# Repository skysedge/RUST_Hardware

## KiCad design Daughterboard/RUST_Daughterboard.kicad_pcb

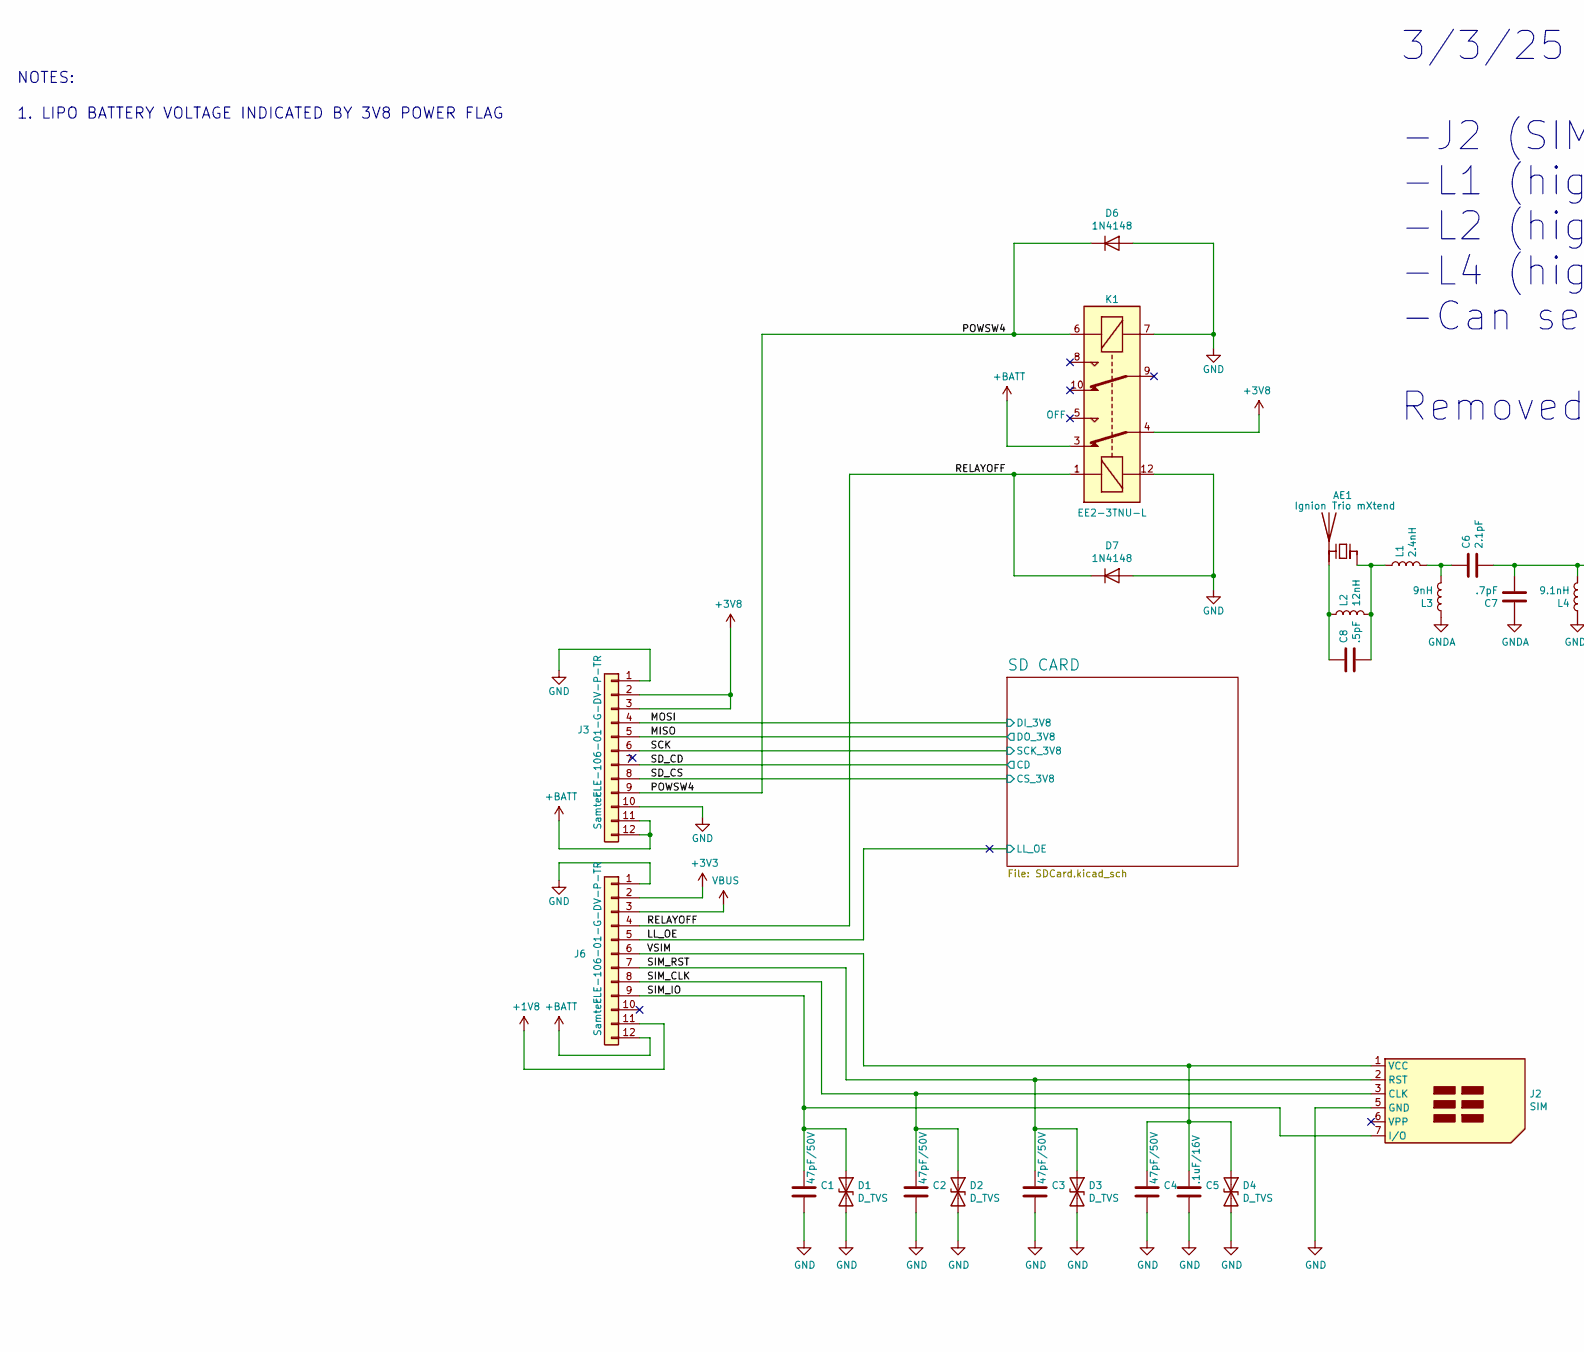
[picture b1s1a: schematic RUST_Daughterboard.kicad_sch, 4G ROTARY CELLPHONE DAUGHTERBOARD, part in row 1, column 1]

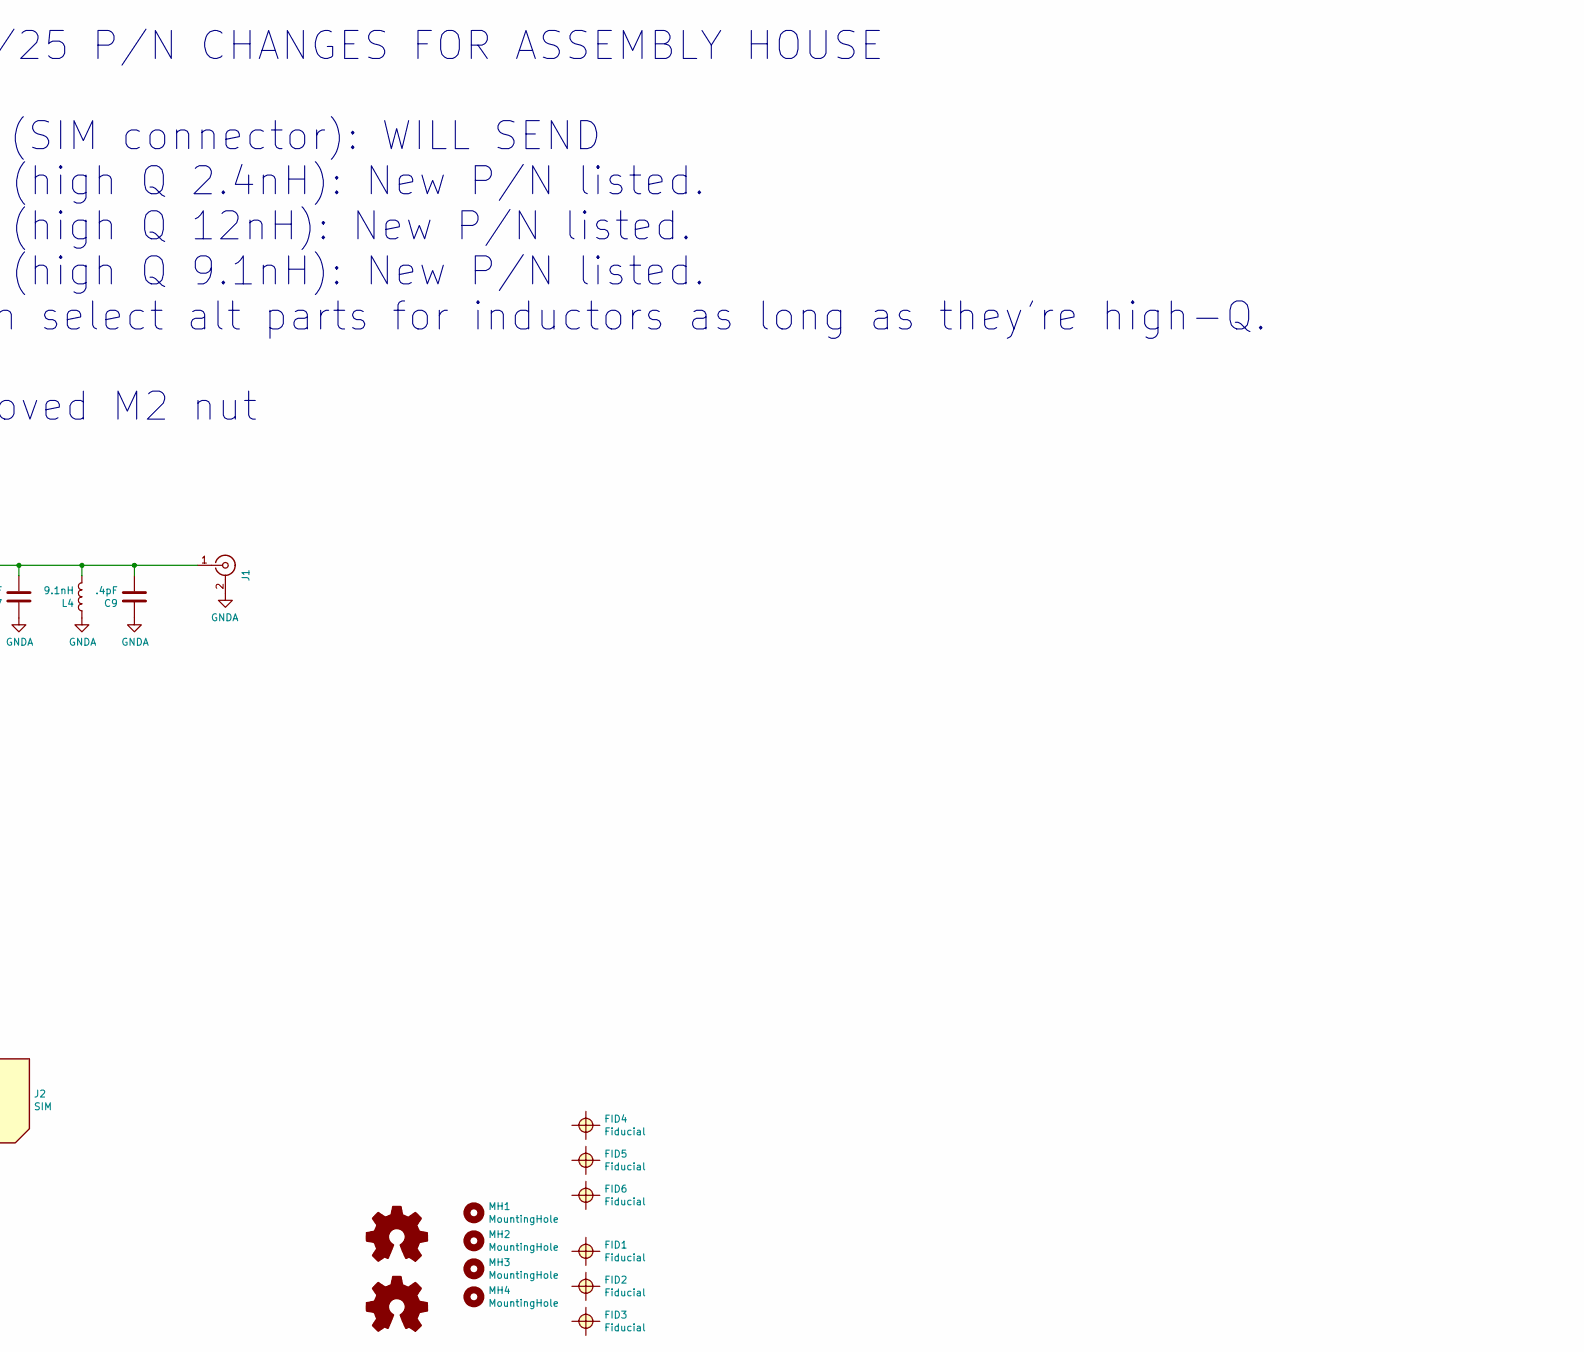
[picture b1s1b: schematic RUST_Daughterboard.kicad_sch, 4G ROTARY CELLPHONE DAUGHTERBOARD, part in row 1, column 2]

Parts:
AE1: Ignion Trio mXtend; Antenna_Ignion_TriomXtend_NN03-310; Mfg. Part No. NN03-310
C1, C2, C3, C4: 47pF/50V; C_0603_1608Metric; Mfg. Part No. GRM1555C1H470JA01D
C5: .1uF/16V; C_0603_1608Metric; Mfg. Part No. C0402C104K4RACTU
C6: 2.1pF; C_0402_1005Metric; Mfg. Part No. GJM1555C1H2R1BB01D
C7: .7pF; C_0402_1005Metric; Mfg. Part No. GJM1555C1HR70BB01D
C8: .5pF; C_0402_1005Metric; Mfg. Part No. 0402N8R2D500CT
C9: .4pF; C_0402_1005Metric; Mfg. Part No. GJM1555C1HR40WB01D
D1, D2, D3, D4: D_TVS; D_0603_1608Metric; Mfg. Part No. PESD0402-140
D6, D7: 1N4148; D_SOD-123; Mfg. Part No. 1N4148W-13-F
FID1, FID2, FID3, FID4, FID5, FID6: Fiducial; Fiducial_0.75mm_Dia_1.5mm_Outer
J1: Conn_Coaxial; U.FL_Molex_MCRF_73412-0110_Vertical; Mfg. Part No. 0734120110
J2: SIM; SIMHolder_Amph7111S2015X02LF; Mfg. Part No. SF7W006S1AR1000
J3, J6: Conn_01x12; Samtec_2x6HeaderSocket_FLE-106-01-G-DV; Mfg. Part No. FLE-106-01-G-DV-P-TR
K1: EE2-3TNU-L; Relay_Kemet_EE2-3TNU; Mfg. Part No. EE2-3TNU
L1: 2.4nH; L_0603_1608Metric; Mfg. Part No. 2-2176075-4
L2: 12nH; L_0603_1608Metric; Mfg. Part No. LQW18AN12NG00D
L3: 9nH; L_0402_1005Metric; Mfg. Part No. LQW15AN9N0G80
L4: 9.1nH; L_0603_1608Metric; Mfg. Part No. LQW18AN9N1C00D
LOGO1: Logo1; SkysEdge_18mm
LOGO2: Logo2; SkysEdge_18mm
MH1, MH2, MH3, MH4: MountingHole; MountingHole_2.2mm_M2

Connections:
+1V8: J6.11
+3V3: J6.2; also elsewhere on the board
+3V8: J3.2, J3.3, K1.4; also elsewhere on the board
+BATT: J3.11, J3.12, J6.12, K1.3
/LL_OE: J6.5; also elsewhere on the board
/MISO: J3.5; also elsewhere on the board
/MOSI: J3.4; also elsewhere on the board
/POWSW4: D6.1 (K), J3.9, K1.6
/RELAYOFF: D7.1 (K), J6.4, K1.1
/SCK: J3.6; also elsewhere on the board
/SD_CD: J3.7; also elsewhere on the board
/SD_CS: J3.8; also elsewhere on the board
/SIM_CLK: C2.1, D2.1 (A1), J2.3 (CLK), J6.8
/SIM_IO: C1.1, D1.1 (A1), J2.7 (I/O), J6.9
/SIM_RST: C3.1, D3.1 (A1), J2.2 (RST), J6.7
/VSIM: C4.1, C5.1, D4.1 (A1), J2.1 (VCC), J6.6
GND: C1.2, C2.2, C3.2, C4.2, C5.2, D1.2 (A2), D2.2 (A2), D3.2 (A2), D4.2 (A2), D6.2 (A), D7.2 (A), J2.5 (GND), J3.1, J3.10, J6.1, K1.7, K1.12; also elsewhere on the board
GNDA: C7.1, C9.1, J1.2 (Ext), L3.1, L4.1
unnamed: AE1.1 (FEED), C8.2, L1.1, L2.2
unnamed: AE1.2 (PCB_Trace), C8.1, L2.1
unnamed: C6.1, L1.2, L3.2
unnamed: C6.2, C7.2, C9.2, J1.1 (In), L4.2
VBUS: J6.3

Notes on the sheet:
3/3/25 P/N CHANGES FOR ASSEMBLY HOUSE -J2 (SIM connector): WILL SEND -L1 (high Q 2.4nH): New P/N listed. -L2 (high Q 12nH): New P/N listed. -L4 (high Q 9.1nH): New P/N listed. -Can select alt parts for inductors as long as they're high-Q. Removed M2 nut
NOTES: 1. LIPO BATTERY VOLTAGE INDICATED BY 3V8 POWER FLAG

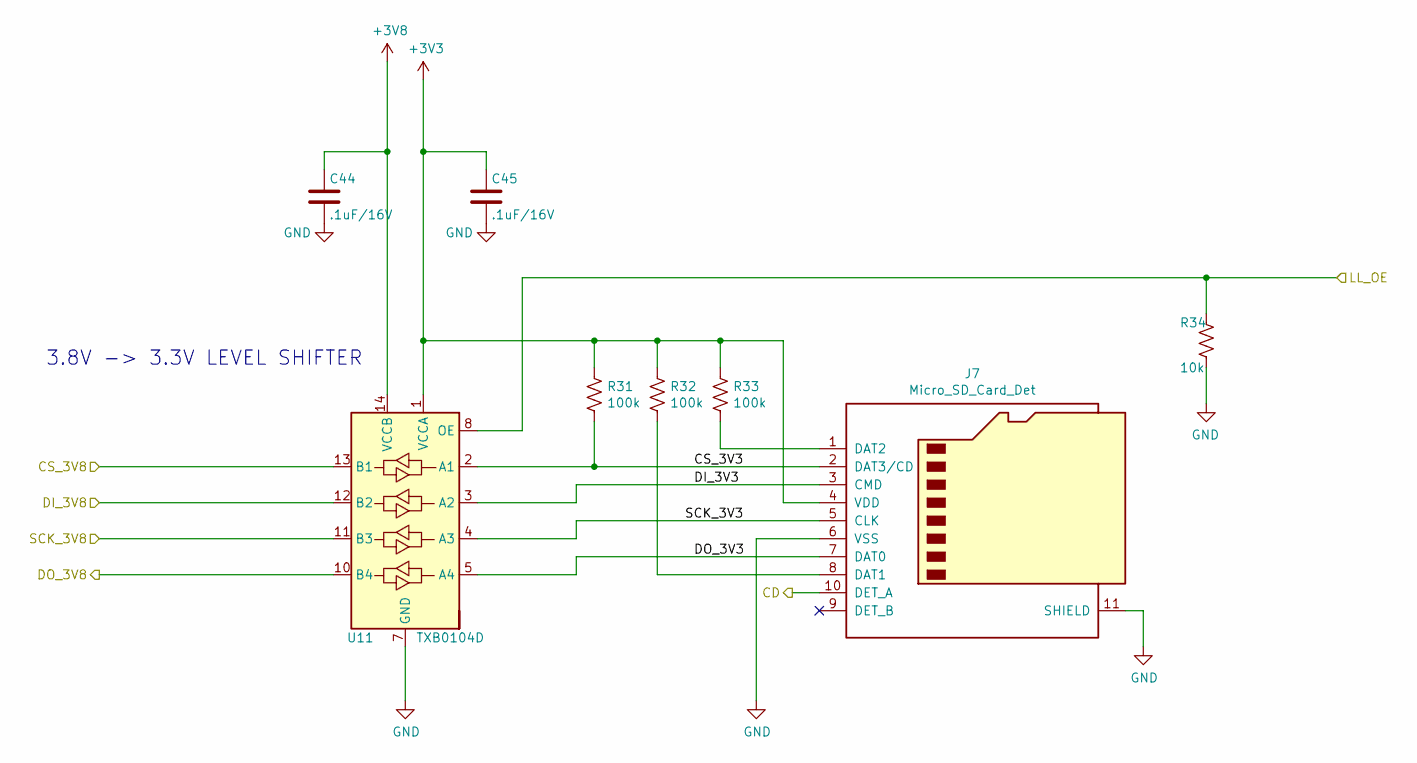
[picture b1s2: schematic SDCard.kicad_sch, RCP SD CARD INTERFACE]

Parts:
C44, C45: .1uF/16V; C_0603_1608Metric; Mfg. Part No. C0402C104K4RACTU
J7: Micro_SD_Card_Det; MicroSDSocket_GCT_MEM2061-01-188-00-A; Mfg. Part No. MEM2061-01-188-00-A
R31, R32, R33: 100k; R_0603_1608Metric; Mfg. Part No. CRG0603F100K
R34: 10k; R_0603_1608Metric; Mfg. Part No. CRG0603J10K
U11: TXB0104D; SOIC-14_3.9x8.7mm_P1.27mm; Mfg. Part No. TXB0104D

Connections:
+3V3: C45.1, J7.4 (VDD), R31.1, R32.1, R33.1, U11.1 (VCCA); also elsewhere on the board
+3V8: C44.1, U11.14 (VCCB); also elsewhere on the board
/LL_OE: R34.1, U11.8 (OE); also elsewhere on the board
/MISO: U11.10 (B4); also elsewhere on the board
/MOSI: U11.12 (B2); also elsewhere on the board
/SCK: U11.11 (B3); also elsewhere on the board
/SD CARD/CS_3V3: J7.2 (DAT3/CD), R31.2, U11.2 (A1)
/SD CARD/DI_3V3: J7.3 (CMD), U11.3 (A2)
/SD CARD/DO_3V3: J7.7 (DAT0), U11.5 (A4)
/SD CARD/SCK_3V3: J7.5 (CLK), U11.4 (A3)
/SD_CD: J7.10 (DET_A); also elsewhere on the board
/SD_CS: U11.13 (B1); also elsewhere on the board
GND: C44.2, C45.2, J7.6 (VSS), J7.11 (SHIELD), R34.2, U11.7 (GND); also elsewhere on the board
unnamed: J7.8 (DAT1), R32.2
unnamed: J7.1 (DAT2), R33.2

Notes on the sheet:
3.8V -> 3.3V LEVEL SHIFTER

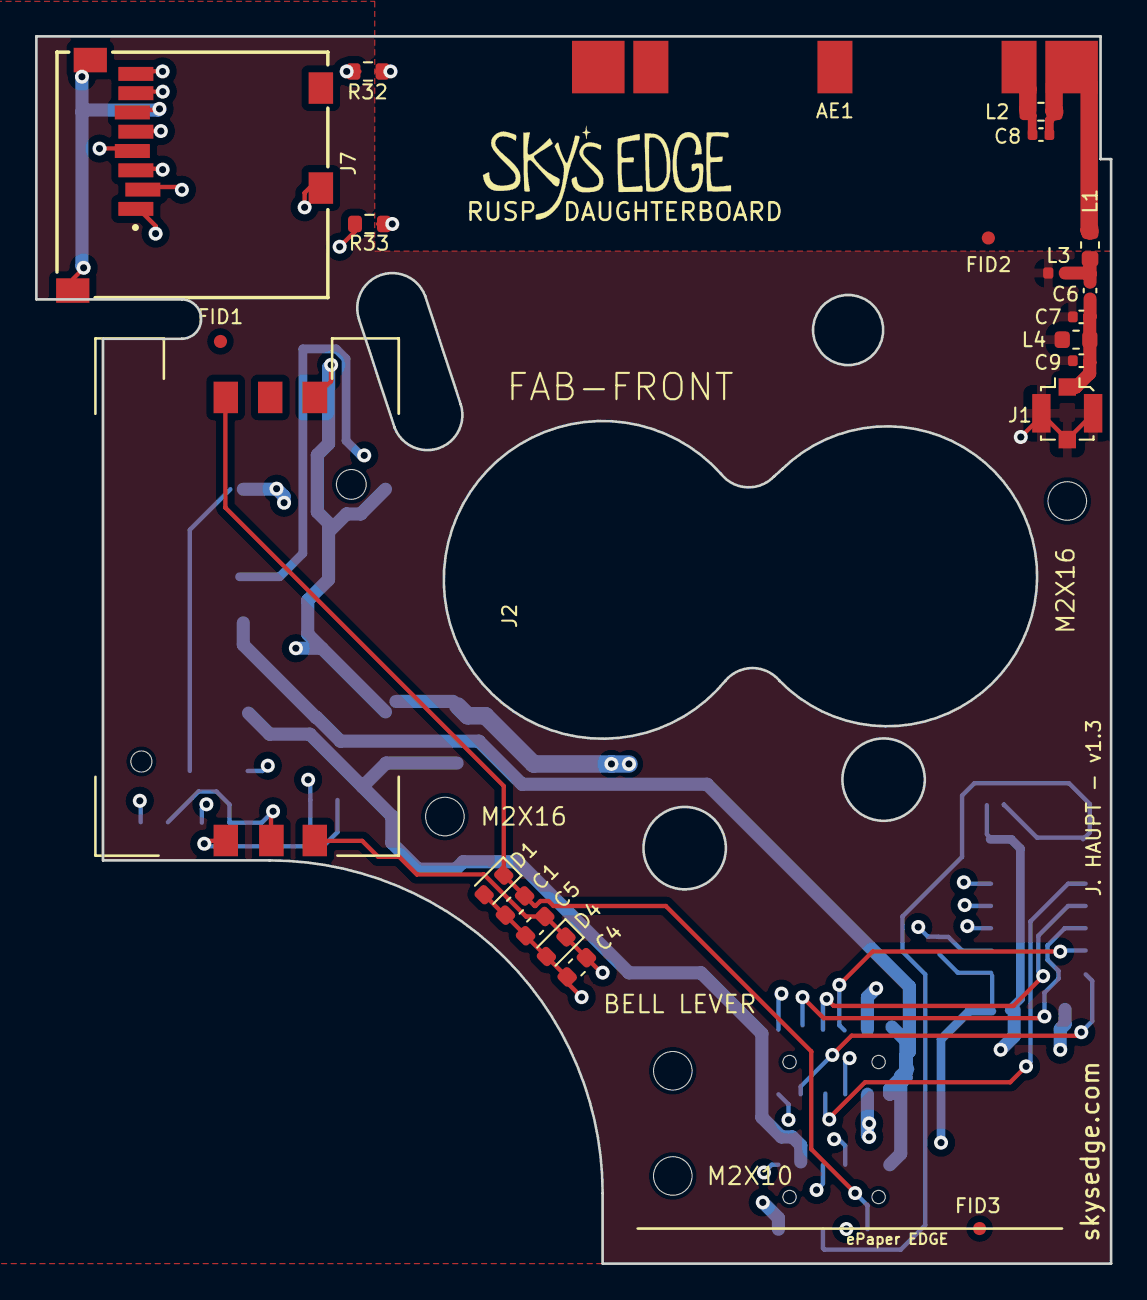
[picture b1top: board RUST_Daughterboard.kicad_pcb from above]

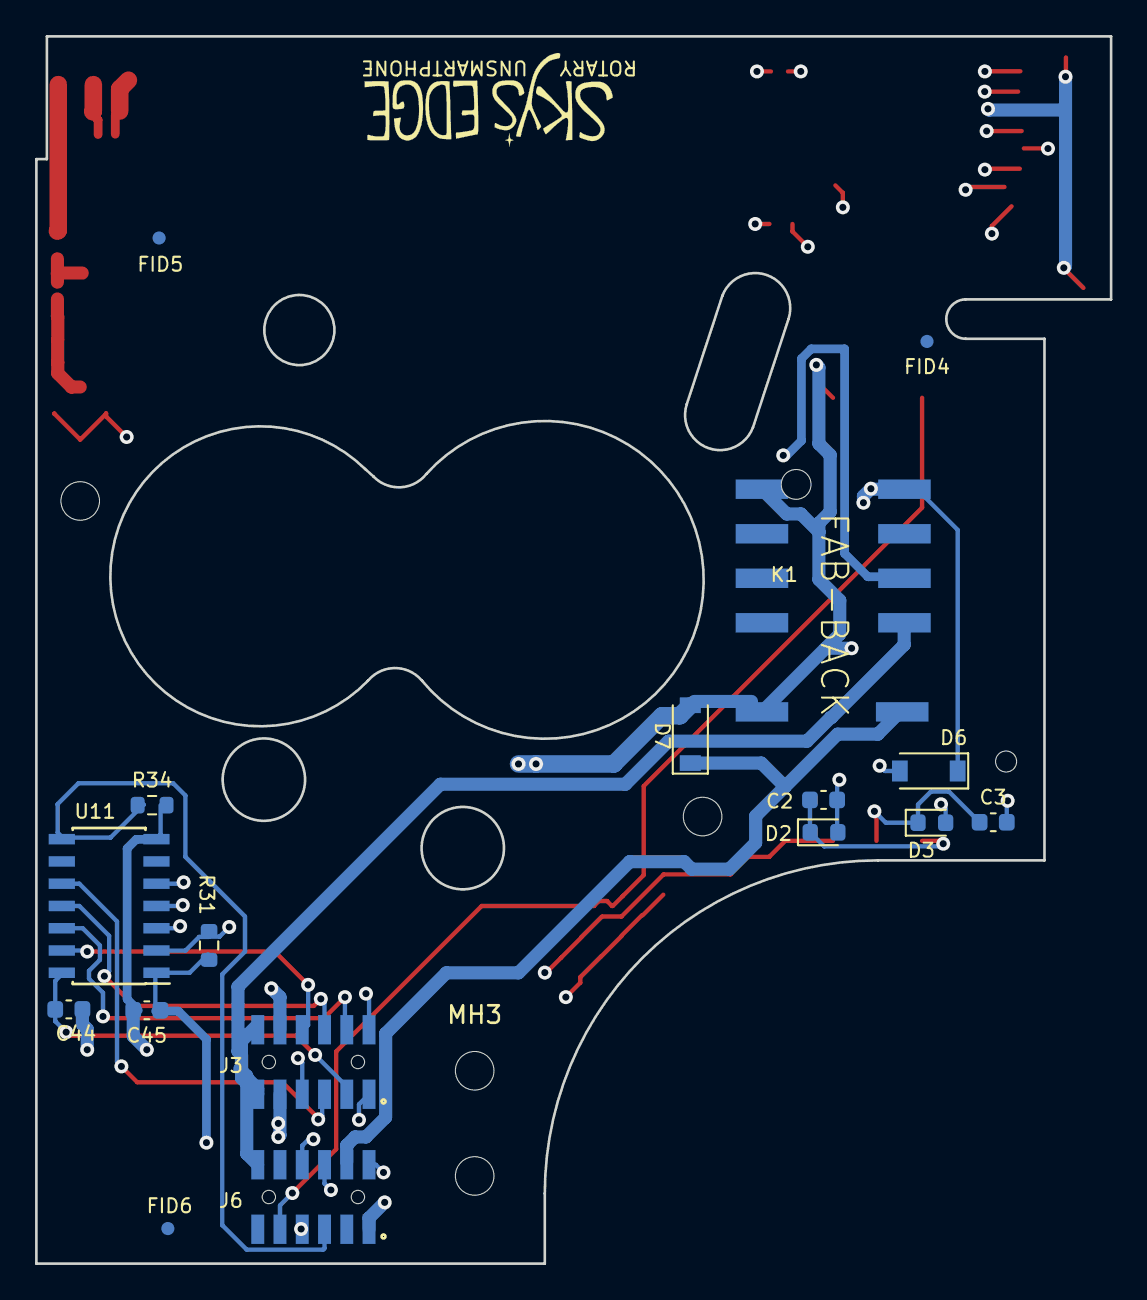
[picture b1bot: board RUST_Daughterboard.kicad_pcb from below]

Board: 4 copper layers, 61.3 x 70.0 mm, 45 parts (19 on the bottom side), 27 nets.

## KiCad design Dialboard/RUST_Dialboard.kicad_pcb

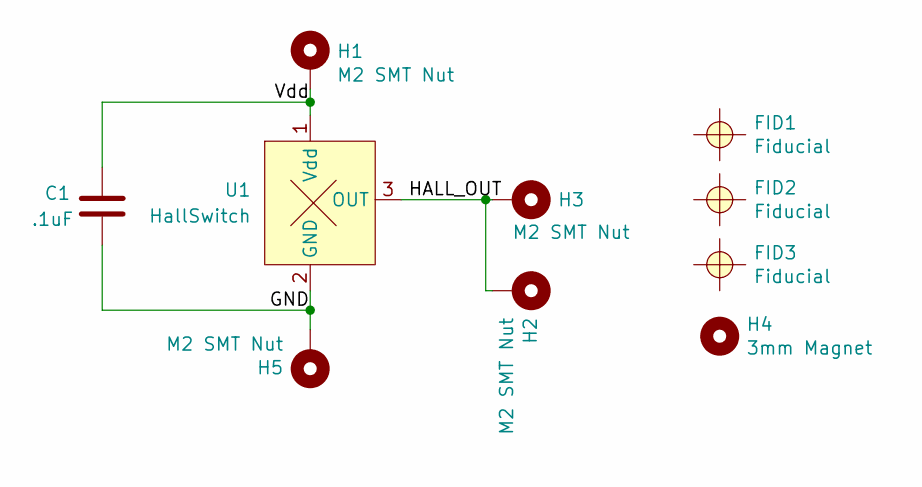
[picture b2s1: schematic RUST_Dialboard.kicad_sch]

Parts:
C1: .1uF; C_0603_1608Metric; Mfg. Part No. 0603B104K250CT
FID1, FID2, FID3: Fiducial; Fiducial_0.75mm_Dia_1.5mm_Outer
H1, H2, H3, H5: M2 SMT Nut; SMTSO-M2-3ET; Mfg. Part No. SMTSO-M2-3ET
H4: 3mm Magnet; 3mmMagnetHole; Mfg. Part No. N42P120060
U1: HallSwitch; SC-59; Mfg. Part No. AH1806-W-7

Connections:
/GND: C1.2, H5.1, U1.2 (GND)
/HALL_OUT: H2.1, H3.1, U1.3 (OUT)
/Vdd: C1.1, H1.1, U1.1 (Vdd)

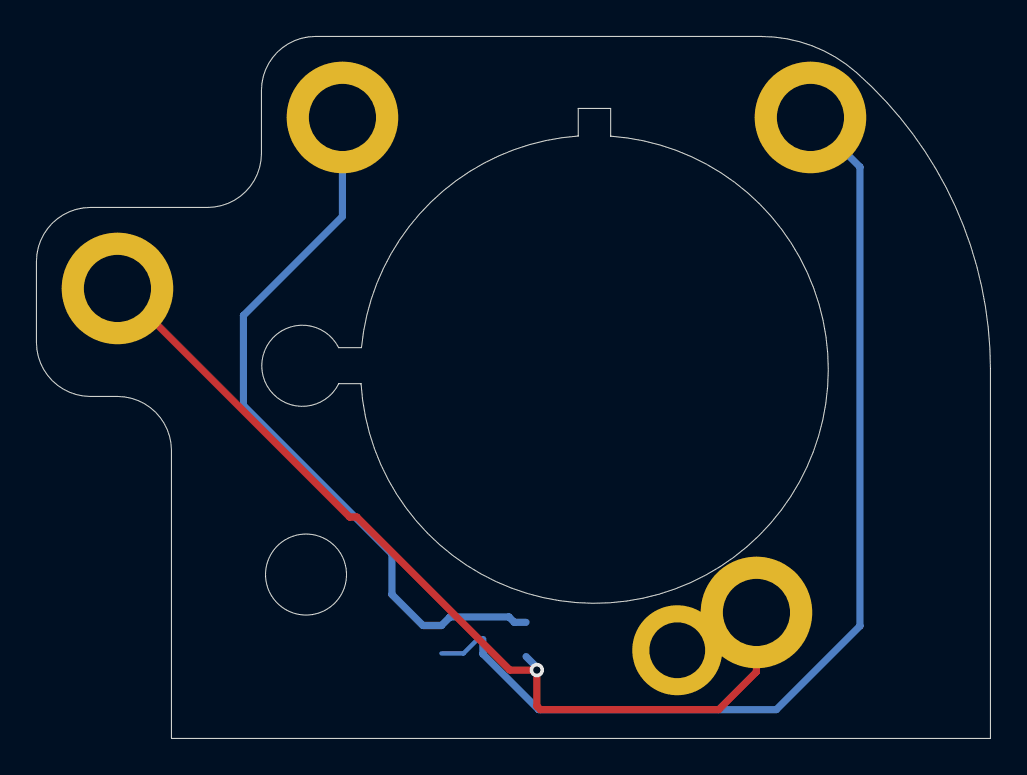
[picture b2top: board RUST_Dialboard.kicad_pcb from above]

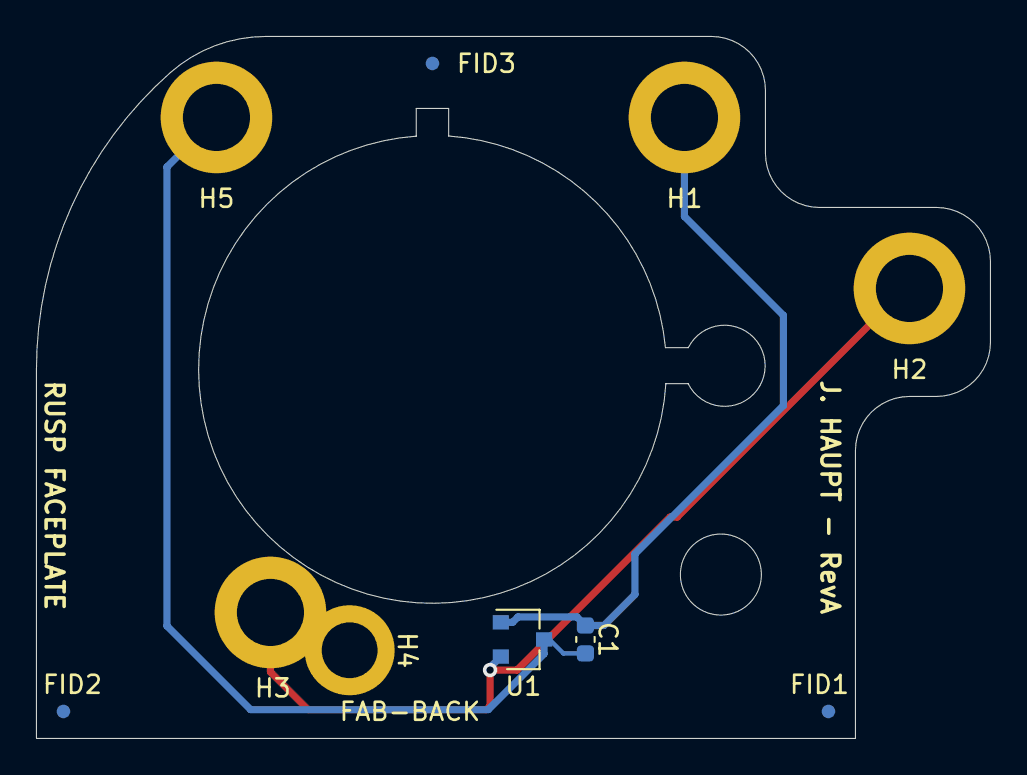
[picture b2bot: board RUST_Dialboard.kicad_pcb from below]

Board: 2 copper layers, 53.0 x 39.0 mm, 10 parts (5 on the bottom side), 3 nets.

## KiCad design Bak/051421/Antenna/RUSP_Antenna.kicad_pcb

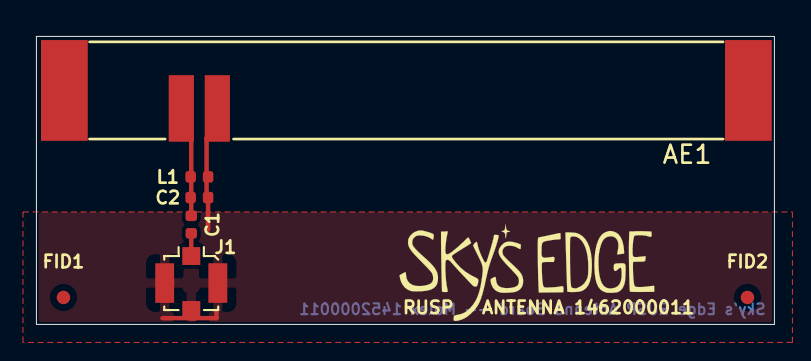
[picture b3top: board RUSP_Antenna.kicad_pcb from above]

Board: 2 copper layers, 41.0 x 16.0 mm, 7 parts (0 on the bottom side), 3 nets.

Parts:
AE1: Antenna_Chip; Antenna_Molex_1462000011
C1: 2.7pF; C_0402_1005Metric
C2: .5pF; C_0402_1005Metric
FID1, FID2: Fiducial; Fiducial_0.75mm_Dia_1.5mm_Outer
J1: uFL; U.FL_Molex_MCRF_73412-0110_Vertical
L1: 7.5nH; L_0402_1005Metric

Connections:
GNDA: AE1.2, C2.2, J1.2, L1.2
unnamed: AE1.1, C1.1, C2.1, L1.1
unnamed: C1.2, J1.1

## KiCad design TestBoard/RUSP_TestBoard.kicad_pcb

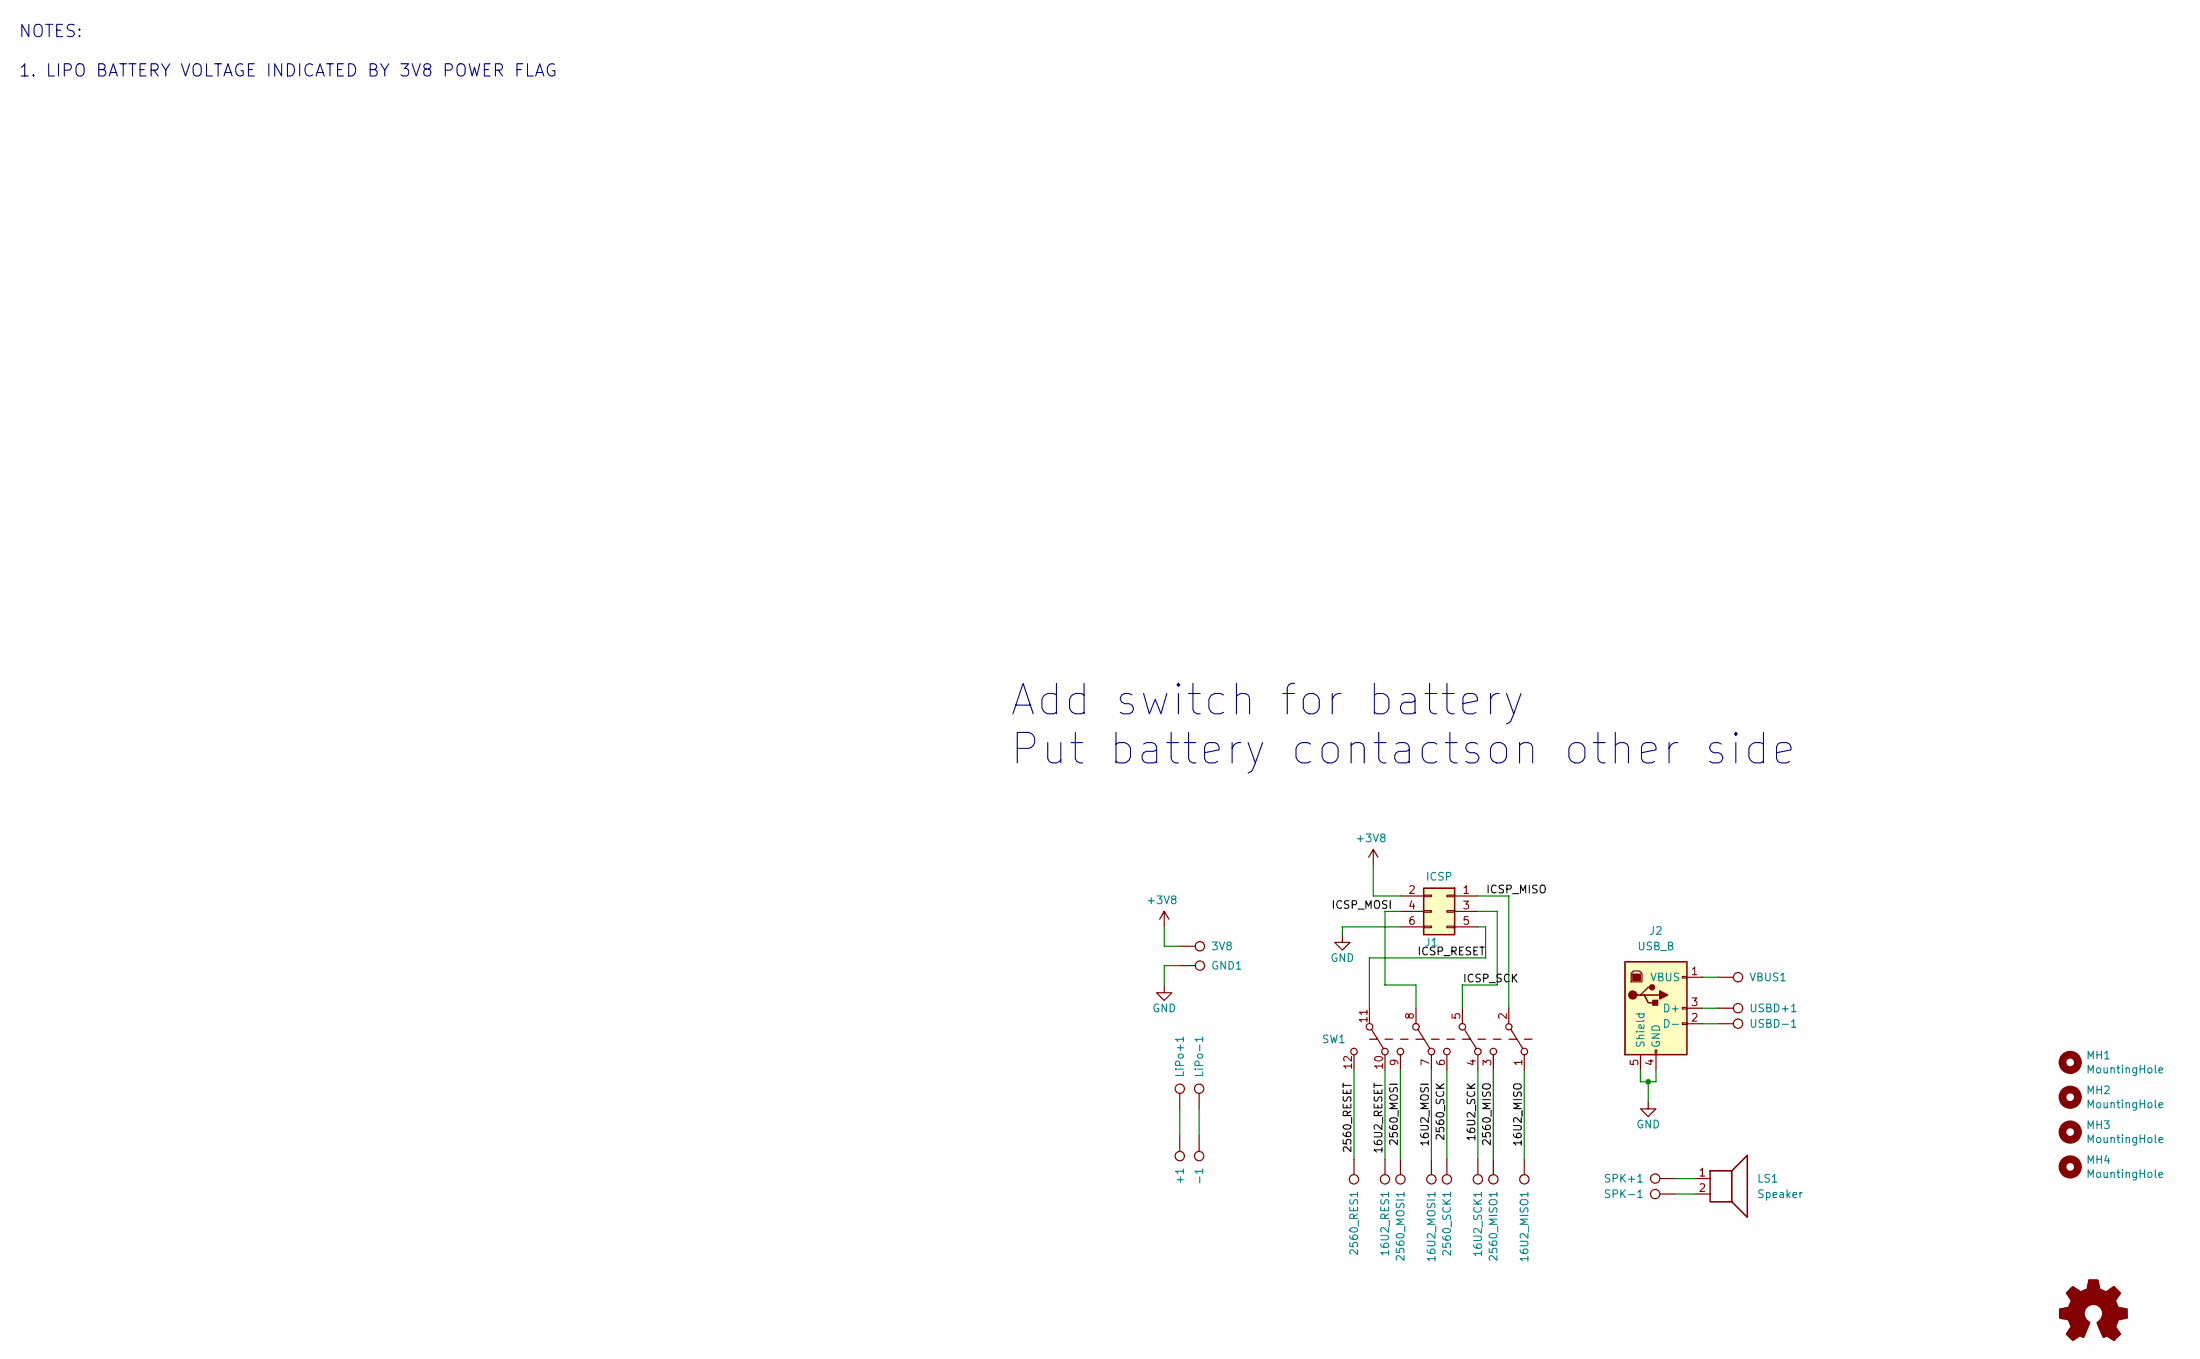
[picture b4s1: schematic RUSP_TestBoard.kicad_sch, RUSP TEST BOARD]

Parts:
3V8, 16U2_MISO1, 16U2_MOSI1, 16U2_RES1, 16U2_SCK1, 2560_MISO1, 2560_MOSI1, 2560_RES1, 2560_SCK1: TestPoint; TestPoint_PogoPin_PreciDip-90055-AS; Mfg. Part No. 90055-AS
+1: TestPoint; TestPoint_PogoPin_PreciDip-90055-AS; Mfg. Part No. 90055-AS
-1: TestPoint; TestPoint_PogoPin_PreciDip-90055-AS; Mfg. Part No. 90055-AS
GND1: TestPoint; TestPoint_PogoPin_PreciDip-90055-AS; Mfg. Part No. 90055-AS
J1: ICSP; ICSP_Header; Mfg. Part No. 75869-131LF
J2: USB_B; USB-B_Amphenol-UE27BC54130; Mfg. Part No. UE27BC54130
LOGO1: Logo1; SkysEdge24mm
LS1: Speaker; Speaker_PUI_AR01232MS-SC12-WP-R; Mfg. Part No. AR01232MS-SC12-WP-R
LiPo+1: TestPoint; TestPoint_Pad_4.0x4.0mm
LiPo-1: TestPoint; TestPoint_Pad_4.0x4.0mm
MH1, MH2, MH3, MH4: MountingHole; MountingHole_3.2mm_M3_Pad
SPK+1: TestPoint; TestPoint_PogoPin_PreciDip-90055-AS; Mfg. Part No. 90055-AS
SPK-1: TestPoint; TestPoint_PogoPin_PreciDip-90055-AS; Mfg. Part No. 90055-AS
SW1: SW_4P2T; Switch_4PDT_ESwitch-EG4208; Mfg. Part No. EG4208
USBD+1: TestPoint; TestPoint_PogoPin_PreciDip-90055-AS; Mfg. Part No. 90055-AS
USBD-1: TestPoint; TestPoint_PogoPin_PreciDip-90055-AS; Mfg. Part No. 90055-AS
VBUS1: TestPoint; TestPoint_PogoPin_PreciDip-90055-AS; Mfg. Part No. 90055-AS

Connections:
+3V8: 3V8.1, J1.2
/16U2_MISO: 16U2_MISO1.1, SW1.1
/16U2_MOSI: 16U2_MOSI1.1, SW1.7
/16U2_RESET: 16U2_RES1.1, SW1.10
/16U2_SCK: 16U2_SCK1.1, SW1.4
/2560_MISO: 2560_MISO1.1, SW1.3
/2560_MOSI: 2560_MOSI1.1, SW1.9
/2560_RESET: 2560_RES1.1, SW1.12
/2560_SCK: 2560_SCK1.1, SW1.6
/ICSP_MISO: J1.1, SW1.2
/ICSP_MOSI: J1.4, SW1.8
/ICSP_RESET: J1.5, SW1.11
/ICSP_SCK: J1.3, SW1.5
GND: GND1.1, J1.6, J2.4 (GND), J2.5 (Shield)
unnamed: +1.1, LiPo+1.1
unnamed: -1.1, LiPo-1.1
unnamed: J2.1 (VBUS), VBUS1.1
unnamed: J2.2 (D-), USBD-1.1
unnamed: J2.3 (D+), USBD+1.1
unnamed: LS1.1, SPK+1.1
unnamed: LS1.2, SPK-1.1

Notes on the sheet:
NOTES: 1. LIPO BATTERY VOLTAGE INDICATED BY 3V8 POWER FLAG
Add switch for battery Put battery contactson other side

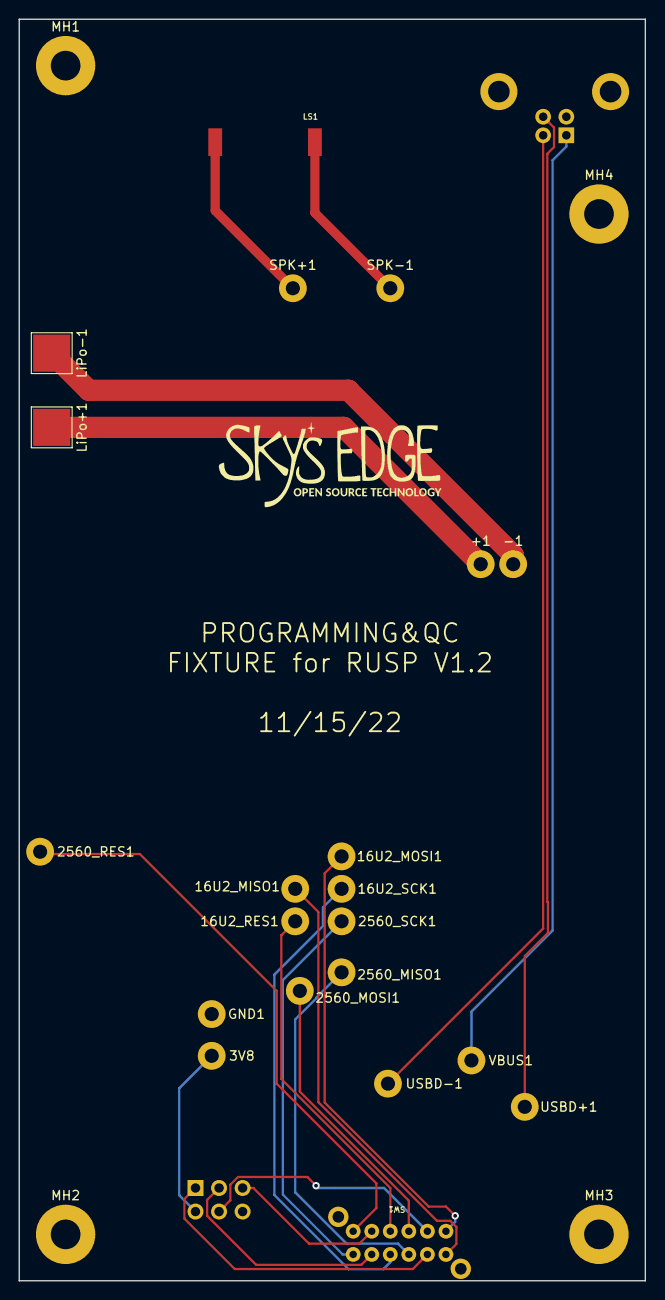
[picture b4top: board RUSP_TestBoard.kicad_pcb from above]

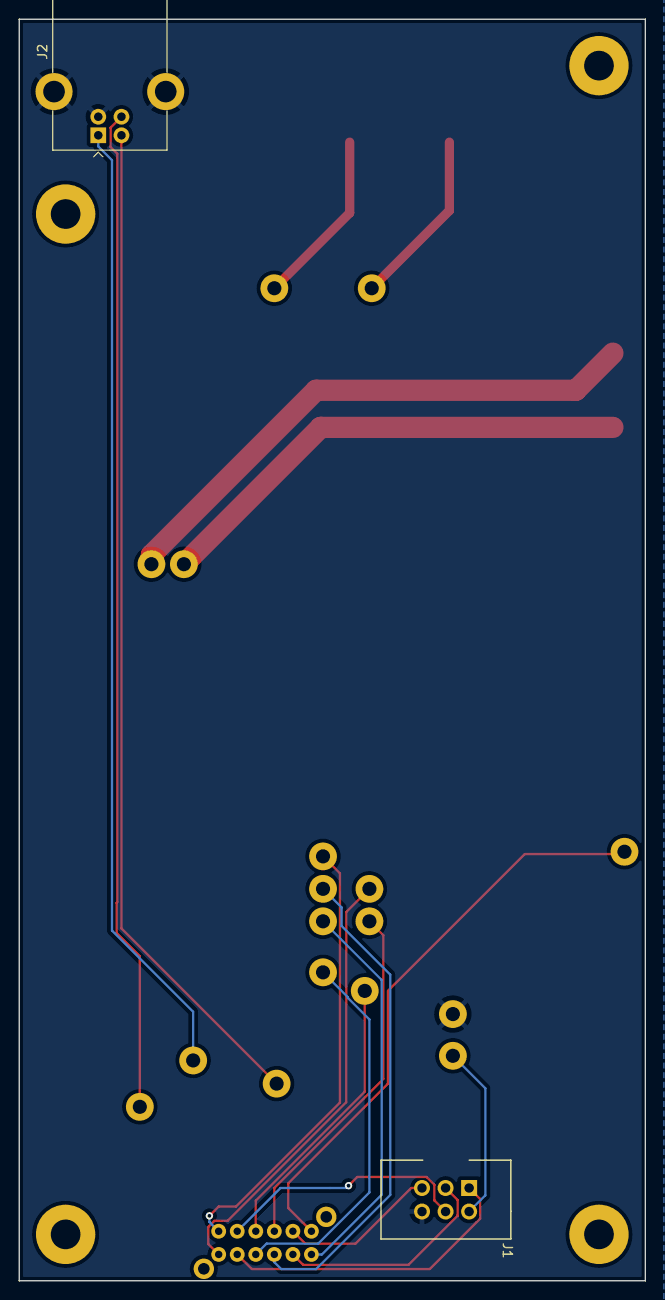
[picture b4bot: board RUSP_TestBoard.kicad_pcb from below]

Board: 2 copper layers, 67.5 x 136.0 mm, 28 parts (2 on the bottom side), 21 nets.

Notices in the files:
parts and their libraries:
Copyright 2016 Accelerated Designs. All rights reserved.
